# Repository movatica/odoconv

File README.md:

# odoconv

**odoconv** ist ein Kunstwort aus *odometer* (engl. für Hodometer bzw. Wegmesser) und *converter*.

Die hier beschriebene elektronische Schaltung konvertiert die Wechselspannung eines Nabendynamos in ein Schaltsignal, mit dem normale Sigma-Fahrradtachos angesteuert werden können.
Damit entfällt die Installation des Reedkontakts am Vorderrad.

Das macht zwar nichts wirklich einfacher, ich finde es so aber eleganter :blush:

## Projektstruktur

- `casing/` enthält das FreeCAD-Projekt für das Gehäuse.
- `circuit/` enthält das KiCAD-Projekt für die Schaltung (Schaltplan und PCB-Layout).
- `odoconv.ino` ist die Quelldatei um den ATtiny85 mit der Arduino IDE zu programmieren.

## Funktionsprinzip

Ein Nabendynamo erzeugt eine ungefilterte Wechselspannung, die Frequenz ist linear zur Drehzahl.
D.h. aus der Frequenz der Wechselspannung kann die Geschwindigkeit direkt berechnet werden.
Dafür gibt es bereits einige Tacho-Selbstbauprojekte.
Statt einen kompletten Tacho selbst zu bauen, kann man auch einfach die Frequenz teilen, um pro Umdrehung genau einen Puls zu erhalten und damit den Reed-Kontakt eines klassischen Tachos zu ersetzen.
Diese Teilung wird hier über den Zählereingang eines ATtiny Mikrocontrollers realisiert.
Dazu muss eine stabilisierte Spannung und ein definiertes Eingangssignal werden.

## Schaltungsaufbau

Die Schaltung besteht aus vier Teilen:

1. Spannungsversorgung: ein Brückengleichrichter und ein Low-Dropout-Spannungsregler erzeugen aus der Dynamo-Wechselspannung stabile 3,3V-Gleichspannung für den Mikrocontroller.
2. Signaleingang: mithilfe zweier Dioden, Widerstände und einem Glättungskondensator wird ein Optokoppler mit einer Phase der Dynamo-Spannung angesteuert. Dieser macht daraus ein sauberes Rechtecksignal für den Zählereingang des Mikrocontrollers.
3. Mikrocontroller: ein ATtiny85 fungiert als Zähler.
4. Signalausgang: ein weiterer Optokoppler schaltet das Tacho-Signal. Der Phototransistor des Optokopplers ersetzt dabei den Reed-Kontakt des Tachos.

## Teileliste

## Mikrocontroller programmieren

### Arduino IDE

In der Arduino IDE sind native Atmel Mikrocontroller standardmäßig nicht vorgesehen. Für ATtiny Mikrocontroller hat David Mellis eine passende [Bibliothek auf GitHub](https://github.com/damellis/attiny) veröffentlicht.

1. Zunächst muss unter *File -> Preferences -> Settings -> Additional boards manager URLs* diese URL eingetragen werden:  
    `https://raw.githubusercontent.com/damellis/attiny/ide-1.6.x-boards-manager/package_damellis_attiny_index.json`
2. Dann muss im *Boardmanager* die Bibliothek "**attiny** by David A. Mellis" in der aktuellen Version installiert werden.
3. Jetzt kann das korrekte Board ausgewählt werden: *Tools -> Board -> attiny -> ATtiny25/45/85*  
    
4. Als Programmer benutze ich einen *Arduino Uno* als ISP. Wie das geht, wird [hier erläutert](https://docs.arduino.cc/built-in-examples/arduino-isp/ArduinoISP). Für die korrekte Verkabelung habe ich mir einen passenden Hat gelötet.  
    
5. Für die Programmierung muss jetzt die Option *Sketch -> Upload Using Programmer* genutzt werden, sonst schlägt sie mit der Meldung `Upload error: A programmer is required to upload` fehl.  

### avr-gcc und avrdude

Unter Linux kann der ATtiny mithilfe des Makefiles auch ohne ArduinoIDE programmiert werden.
Dazu muss die `avr-libc` als Basisbibliothek, `avr-gcc` für das Übersetzen des Quellcodes und `avrdude` für die Programmierung per ISP installiert sein.
Für Debian-basierte Systeme z.B. so:
    `# apt-get install avr-gcc avr-libc avrdude`

Ist alles installiert, wird der Quellcode mit `make all` übersetzt.

Zur Programmierung des ATtiny wird der gleiche Aufbau mit ArduinoISP verwendet, wie im vorigen Abschnitt beschrieben. `make program` beschreibt den Mikrocontroller. Gegebenenfalls muss die Konfiguration des Programmers am Anfang des Makefiles angepasst werden.

## Limitierungen

Der eingesetzte Spannungsregler ist nur bis 25V (Peak 60V) ausgelegt.
Da die gesamte Schaltung absichtlich sehr wenig Strom verbraucht, muss am Dynamo eine zusätzliche Last, z.B. eine Lampe, betrieben werden!
Bei normaler Last pendelt sich die Dynamo-Spannung bei ca. 6,3V ein. Ohne Last steigt die Spannung quasi unbegrenzt, proportional zur Geschwindigkeit. Bei z.B. Bergabfahrten mit > 30 kmh können Spannungen über 100V auftreten, die die Schaltung nicht verträgt.

Die einfachste und gängige Lösung ist der Dauerbetrieb des Fahrradlichts.

Alternativ kann entweder ein einfaches Schaltnetzteil konstruiert werden, was die Schaltung unverhältnismäßig komplex machen würde. Oder man ersetzt die Spannungsversorgung durch eine Knopfzelle, was sinnloserweise noch eine weitere Stromquelle (neben dem Dynamo und der Tacho-Batterie) einführen würde.

## ToDo

- [ ] Signaleingang optimieren, hier könnten weniger Bauteile sein
- [ ] Die Optokoppler brauchen viel Platz, vllt können die wegoptimiert werden.
- [ ] Gehäuse als Dock für den Tacho bauen, spart Umbauten am Kabel und Platz am Fahrrad
- [ ] Programmier-/Debug-Schnittstelle für den ATTiny direkt auf der Platine
- [ ] Projektdoku zweisprachig deutsch/englisch

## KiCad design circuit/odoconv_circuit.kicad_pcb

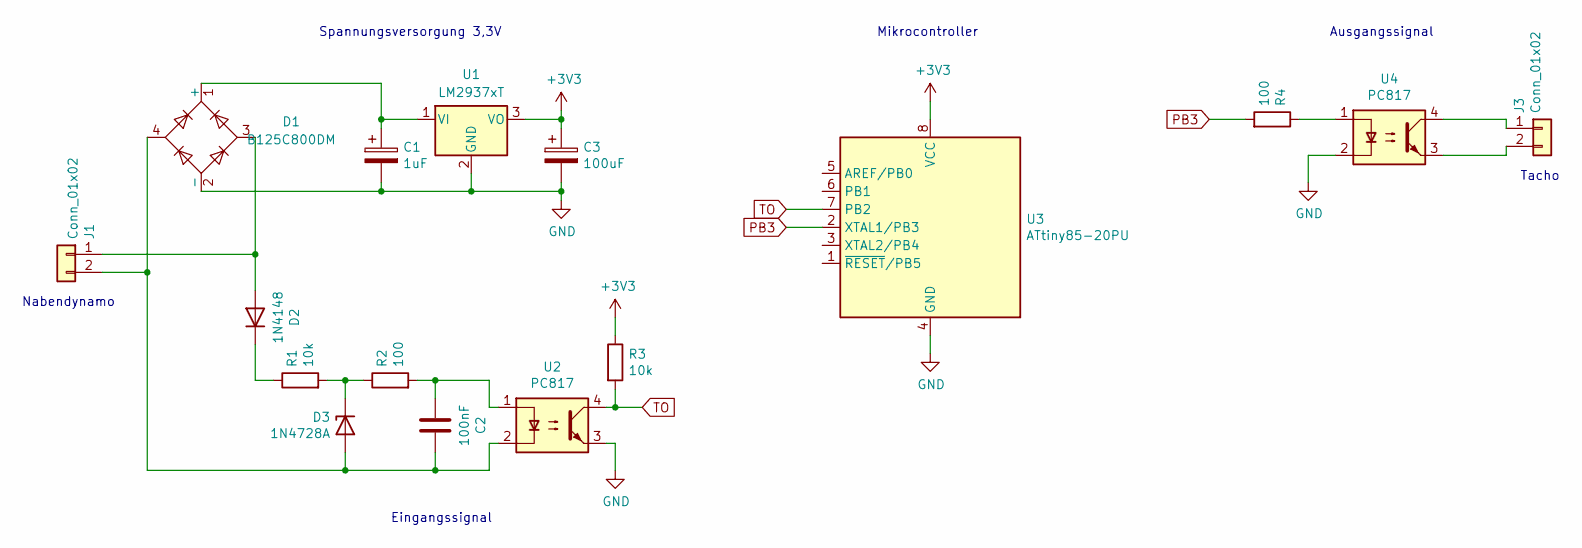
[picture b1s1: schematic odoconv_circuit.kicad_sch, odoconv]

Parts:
C1: 1uF; CP_Elec_4x5.4
C2: 100nF; C_0805_2012Metric_Pad1.18x1.45mm_HandSolder
C3: 100uF; CP_Elec_5x5.4
D1: B125C800DM; Diode_Bridge_DIP-4_W7.62mm_P5.08mm
D2: 1N4148; D_DO-35_SOD27_P7.62mm_Horizontal
D3: 1N4728A; D_DO-41_SOD81_P10.16mm_Horizontal
J1, J3: Conn_01x02; PinHeader_1x02_P2.54mm_Vertical
R1, R3: 10k; R_0805_2012Metric_Pad1.20x1.40mm_HandSolder
R2, R4: 100; R_0805_2012Metric_Pad1.20x1.40mm_HandSolder
U1: LM2937xT; TO-220-3_Vertical
U2, U4: PC817; DIP-4_W7.62mm
U3: ATtiny85-20PU; DIP-8_W7.62mm

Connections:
+3V3: C3.1, R3.1, U1.3 (VO), U3.8 (VCC)
GND: C1.2, C3.2, D1.2 (-), U1.2 (GND), U2.3, U3.4 (GND), U4.2
unnamed: C2.1, R2.2, U2.1
unnamed: C1.1, D1.1 (+), U1.1 (VI)
unnamed: D1.3, D2.2 (A), J1.1
unnamed: D2.1 (K), R1.1
unnamed: C2.2, D1.4, D3.2 (A), J1.2, U2.2
unnamed: D3.1 (K), R1.2, R2.1
unnamed: J3.1, U4.4
unnamed: J3.2, U4.3
unnamed: R4.1, U4.1
PB3: R4.2, U3.2 (XTAL1/PB3)
TO: R3.2, U2.4, U3.7 (PB2)

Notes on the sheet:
Spannungsversorgung 3,3V
Ausgangssignal
Nabendynamo
Eingangssignal
Mikrocontroller
Tacho

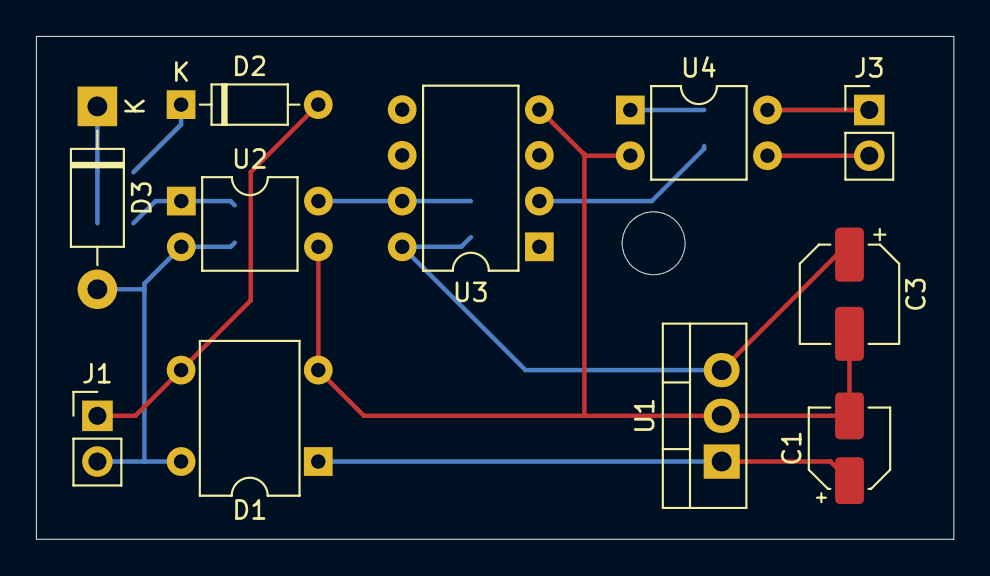
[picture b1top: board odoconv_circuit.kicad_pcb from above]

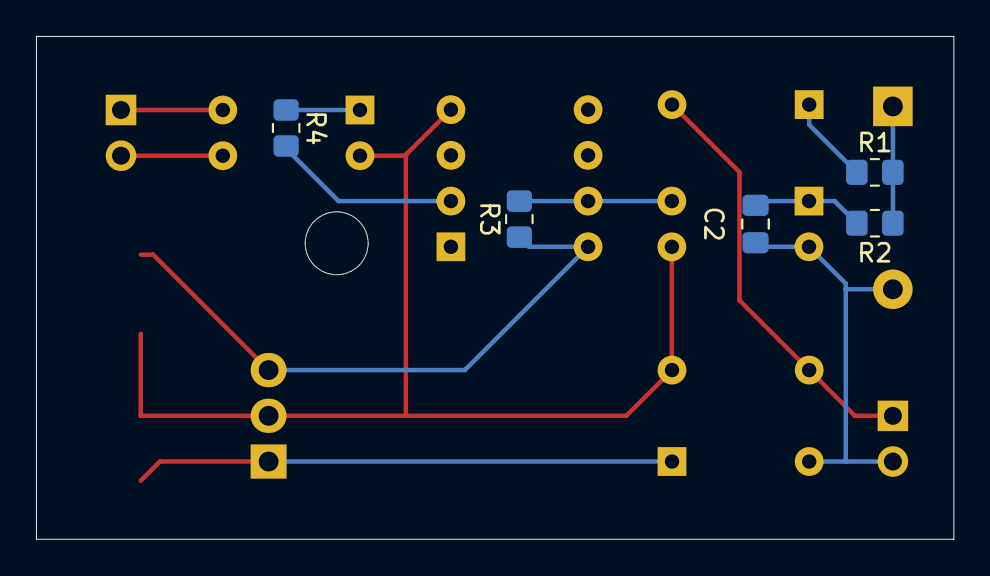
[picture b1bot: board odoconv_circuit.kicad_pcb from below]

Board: 2 copper layers, 51.0 x 27.9 mm, 16 parts (5 on the bottom side), 13 nets.

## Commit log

2023-08-09 Readme fixes
2023-08-09 Added more KiCAD files to .gitignore
2023-08-09 Improve documentation of the programming procedure
2023-08-09 Added documentation about limitations
2023-11-24 Improve power management
2023-11-24 Add Makefile for programming with avrgcc/avrdude
